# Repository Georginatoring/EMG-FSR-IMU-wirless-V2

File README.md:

# EMG-FSR-IMU-wirless-V2
Firmware, software, SCH, BRD, and Solidworks files for EMG FSR IMU band

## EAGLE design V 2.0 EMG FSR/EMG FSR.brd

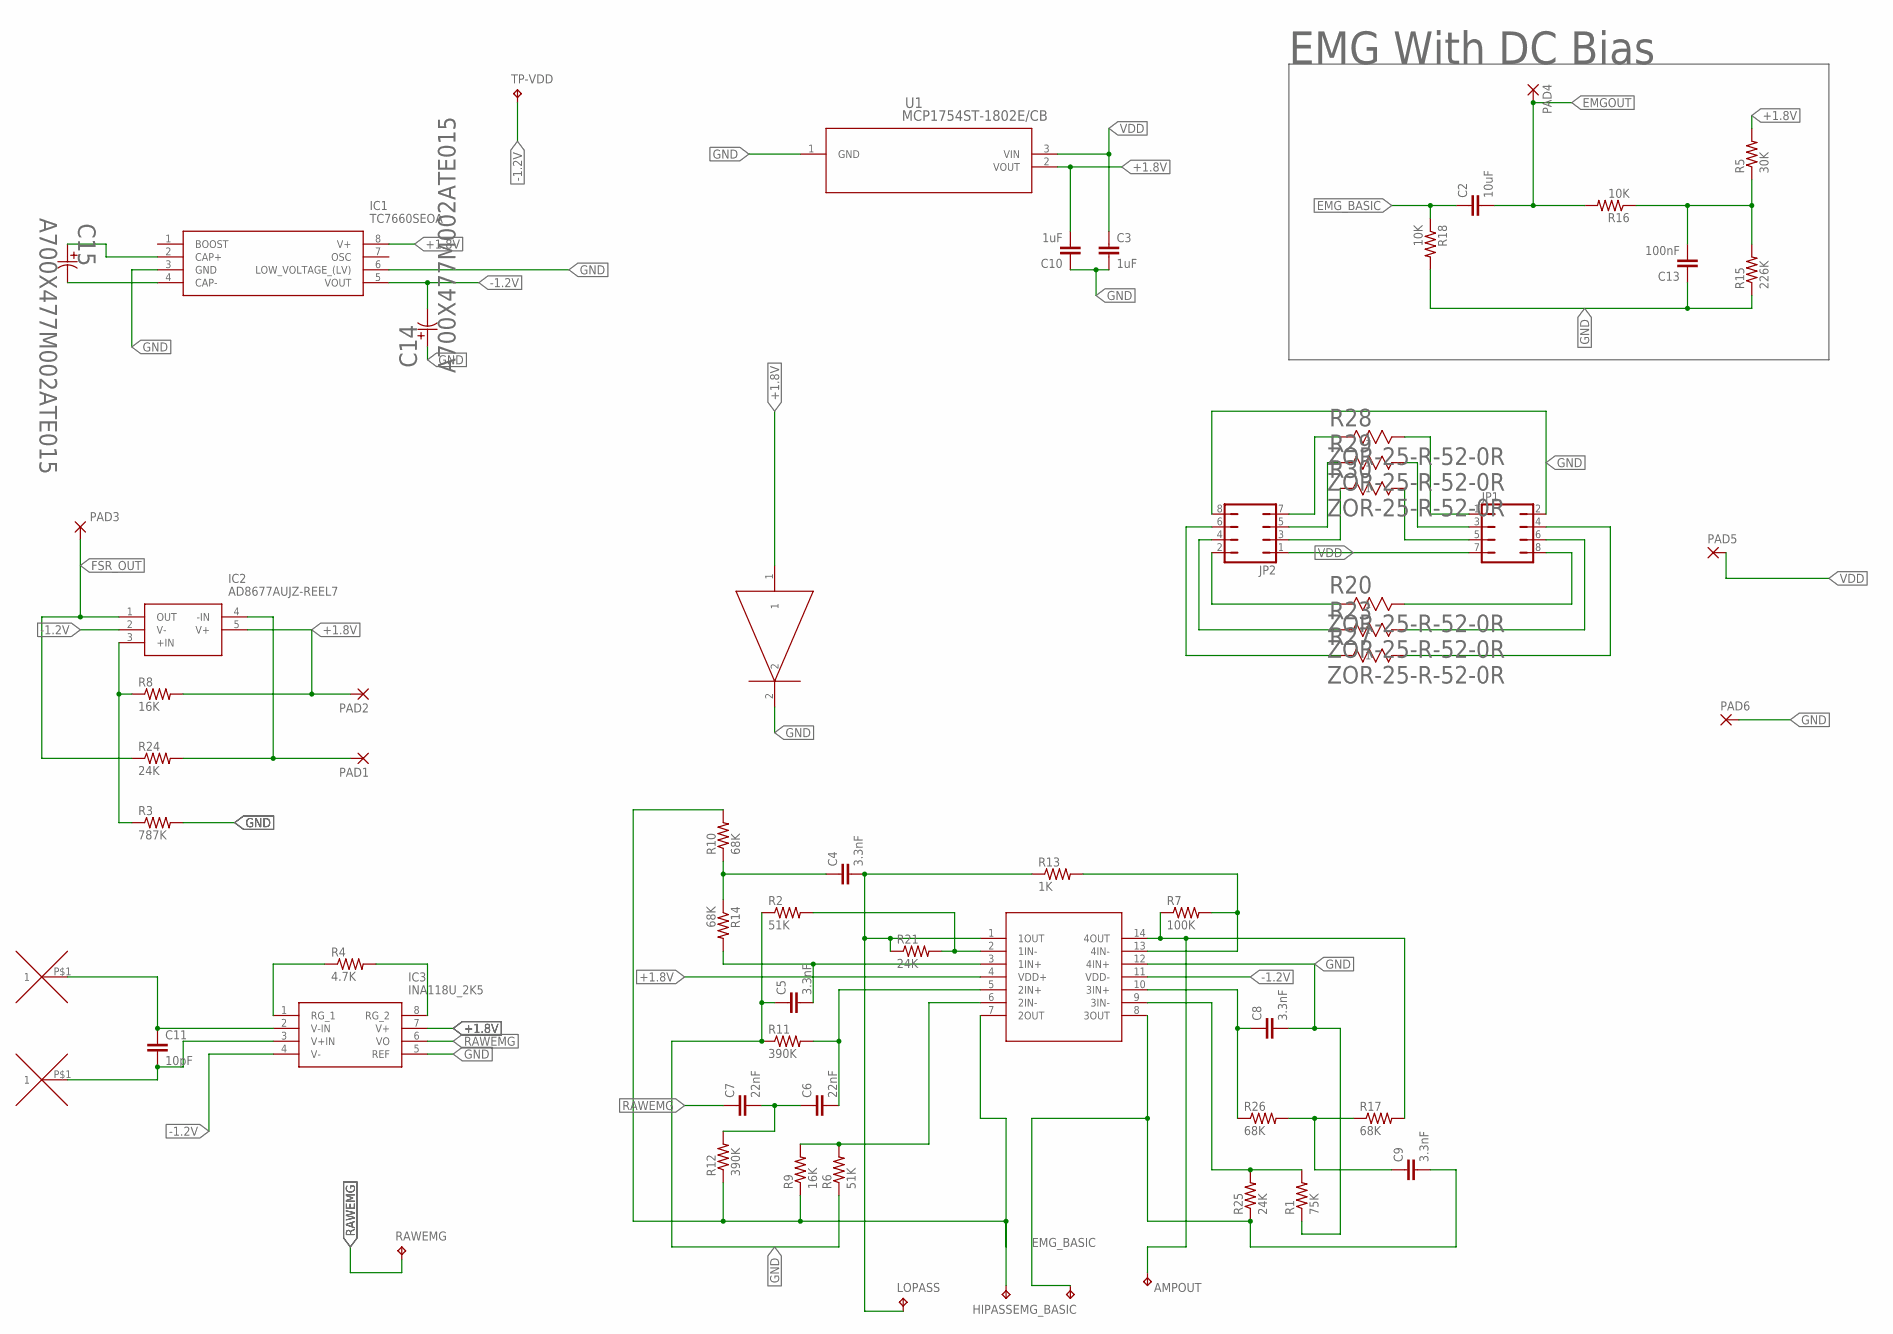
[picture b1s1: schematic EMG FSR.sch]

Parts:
AMPOUT: TPTP08R; TP08R
C2: 10uF; C0402
C3, C10: 1uF; C0402
C4, C5, C8, C9: 3.3nF; C1206
C6, C7: 22nF; C0805
C11: 10pF; C0402
C13: 100nF; C0402
C14, C15: A700X477M002ATE015; PCAP7343-43_KEMET_KEM
EMG_BASIC: TPTP08R; TP08R
HIPASS: TPTP08R; TP08R
IC1: TC7660SEOA; SOIC127P600X175-8N
IC2: AD8677AUJZ-REEL7; SOT95P280X100-5N
IC3: INA118U_2K5; SOIC127P600X175-8N
JP1, JP2: JP4Q
LOPASS: TPTP08R; TP08R
PAD1, PAD2: SMD2; SMD1,27-2,54
PAD3, PAD4, PAD5, PAD6: 1,6/0,8
R1: 75K; R0402
R2, R6: 51K; R0402
R3: 787K; R0805
R4: 4.7K; R0402
R5: 30K; R0402
R7: 100K; R1005
R8, R9: 16K; R0402
R10, R14, R17, R26: 68K; R0402
R11, R12: 390K; R0603
R13: 1K; R0402
R15: 226K; R0402
R16, R18: 10K; R0402
R20, R23, R27, R28, R29, R30: ZOR-25-R-52-0R; RES_ZOR25_6P3X2P3_YAG
R21, R24, R25: 24K; R0402
RAWEMG: TPTP08R; TP08R
RED: RESC0402X40N
TP-VDD: TPTP08R; TP08R
U1: MCP1754ST-1802E/CB; SOT-23A_MC_MCH
U$1: TLC2274-HT; SOP65P640X120-14N
U$2, U$3: EMG_VIA

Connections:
+1.8V: C10.2, IC1.8 (V+), IC2.5 (V+), IC3.7 (V+), PAD2.1, R5.2, R8.2, RED.1, U1.2 (VOUT), U$1.4 (VDD+)
-1.2V: C14.2, IC1.5 (VOUT), IC2.2 (V-), IC3.4 (V-), TP-VDD.TP, U$1.11 (VDD-)
EMGOUT: C2.2, PAD4.1, R16.2
EMG_BASIC: C2.1, C9.2, EMG_BASIC.TP, R18.1, R25.1, U$1.8 (3OUT)
FSR_OUT: IC2.1 (OUT), PAD3.1, R24.1
GND: C3.2, C5.1, C8.2, C10.1, C13.1, C14.1, IC1.3 (GND), IC1.6 (LOW_VOLTAGE_(LV)), IC3.5 (REF), JP1.2, JP2.8, PAD6.1, R1.1, R2.1, R3.2, R6.1, R11.1, R15.1, R18.2, RED.2, U1.1 (GND), U$1.12 (4IN+)
unnamed: C15.1, IC1.2 (CAP+)
unnamed: C15.2, IC1.4 (CAP-)
unnamed: C11.1, IC3.2 (V-IN), U$2.P$1
unnamed: C11.2, IC3.3 (V+IN), U$3.P$1
unnamed: IC2.4 (-IN), PAD1.1, R24.2
unnamed: C13.2, R5.1, R15.2, R16.1
unnamed: JP2.3, R30.1
unnamed: IC2.3 (+IN), R3.1, R8.1
unnamed: JP1.5, R30.2
unnamed: IC3.1 (RG_1), R4.1
unnamed: IC3.8 (RG_2), R4.2
unnamed: C4.2, LOPASS.TP, R13.1, R21.1, U$1.1 (1OUT)
unnamed: JP2.5, R29.1
unnamed: JP1.3, R29.2
unnamed: AMPOUT.TP, R7.1, R17.2, U$1.14 (4OUT)
unnamed: R7.2, R13.2, U$1.13 (4IN-)
unnamed: R2.2, R21.2, U$1.2 (1IN-)
unnamed: C5.2, R14.2, U$1.3 (1IN+)
unnamed: C4.1, R10.1, R14.1
unnamed: JP1.1, R28.2
unnamed: C6.1, C7.2, R12.2
unnamed: C6.2, R11.2, U$1.5 (2IN+)
unnamed: JP2.7, R28.1
unnamed: R6.2, R9.2, U$1.6 (2IN-)
unnamed: C9.1, R17.1, R26.2
unnamed: C8.1, R26.1, U$1.10 (3IN+)
unnamed: JP2.2, R20.1
unnamed: R1.2, R25.2, U$1.9 (3IN-)
unnamed: JP1.8, R20.2
unnamed: JP1.6, R23.2
unnamed: JP2.4, R23.1
unnamed: JP2.6, R27.1
unnamed: JP1.4, R27.2
PIN7: HIPASS.TP, R9.1, R10.2, R12.1, U$1.7 (2OUT)
RAWEMG: C7.1, IC3.6 (VO), RAWEMG.TP
VDD: C3.1, JP1.7, JP2.1, PAD5.1, U1.3 (VIN)

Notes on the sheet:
EMG With DC Bias

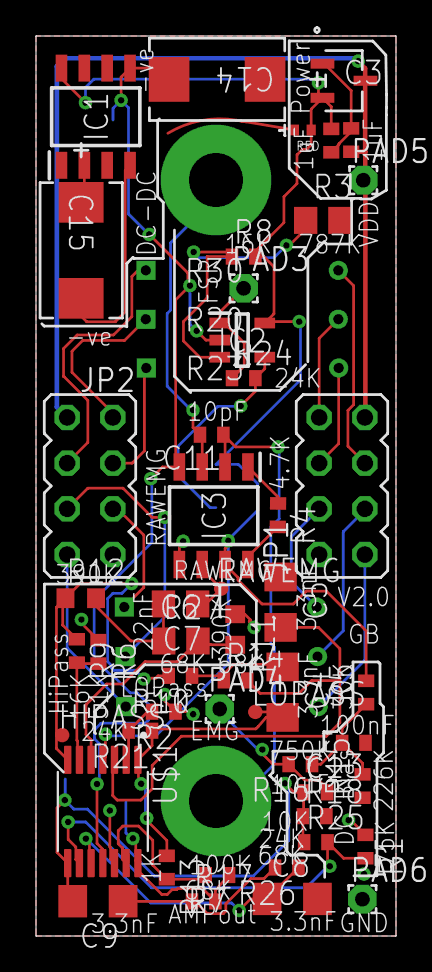
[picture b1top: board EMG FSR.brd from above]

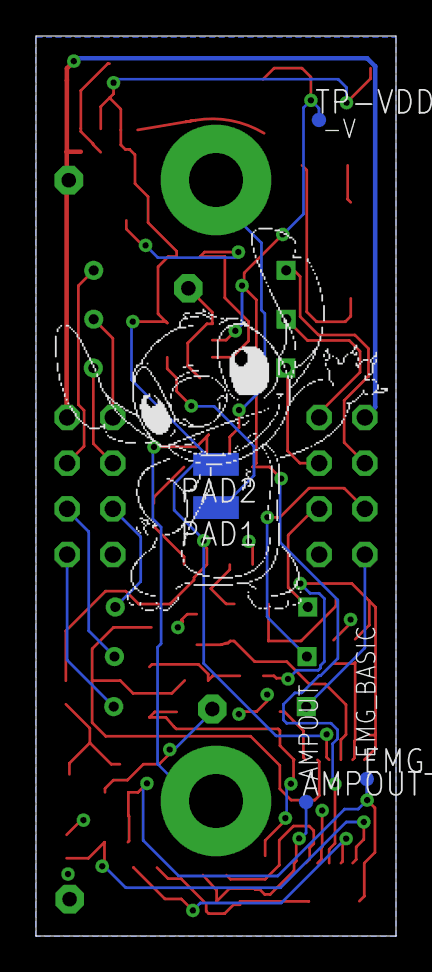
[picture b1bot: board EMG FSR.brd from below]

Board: 2 copper layers, 20.0 x 50.0 mm, 63 parts (5 on the bottom side), 42 nets.

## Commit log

2021-05-03 Add files via upload
    sender and receiver code
2021-05-08 Add files via upload
    Final firmware code.
    added timestamp, fixed IMU bug, increased SPS to 860
2021-05-10 Add files via upload
    Sledworks and Eagle Files

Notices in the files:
parts and their libraries:
COPYRIGHT: Copyright (C) 2018 Accelerated Designs. All rights reserved
